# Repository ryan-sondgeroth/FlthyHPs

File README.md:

# FlthyHPs (Flthy Holoprojectors)

This repo contains the `FlthyHPs_v2.1.ino` sketch and supporting documentation for controlling 3 R2 holoprojectors (Front/Rear/Top) with:

- NeoPixel LED effects (7 LEDs per projector)
- Servo articulation through an Adafruit PCA9685 I2C board
- Auto-twitch behavior for both LEDs and servos
- Serial/I2C command control (plus optional RC input)

This README is based on the manual in [`docs/Guide to Using Your FlthyHPs v1.8 .docx`](docs/Guide%20to%20Using%20Your%20FlthyHPs%20v1.8%20.docx), with updates aligned to the current `v2.1` sketch.

## At a Glance

- **Sketch:** `FlthyHPs_v2.1.ino`
- **Arduino I2C address:** `0x19` (decimal 25)
- **PCA9685 I2C address:** `0x40` (default)
- **Serial baud:** `9600`
- **HP count:** 3 (Front, Rear, Top)

## Hardware

## PCB Renders

| Top | Isometric Front |
|-----|----------------|
|  |  |

| Isometric Back | Side |
|---------------|------|
|  |  |

---

### FlthyHPs Maestro v3 PCB (current)

The v3 system replaces the separate breakout board + PCA9685 combo with a single custom PCB: **FilthyHPs_Maestro**.

- **Arduino Pro Mini** (5V, 16MHz) — plugs into U1 headers
- **Pololu Micro Maestro 6-Channel** servo controller — plugs into U2 headers (replaces PCA9685)
- **Pololu D24V50F5** 5V 5A regulator — plugs into U3 headers
- 6 servos (2 per HP) via Maestro channels 0–5
- 3 HP NeoPixel assemblies (7 LED Jewel each) via Arduino D2/D3/D4
- I2C headers (J6, J7) for external peripherals and accepting commands from I2C controllers
- Serial header (J2) for sending commands to the Arduino sketch

**Power input:**
- 7–36V unregulated via J1 screw terminal (regulated on-board by D24V50F5)
- Or regulated 5V direct via J8 screw terminal (bypasses regulator)

**Improved circuit protection over previous versions:**
- P-ch MOSFET (Q1) ideal diode gates VIN_RAW to the servo rail, preventing backfeed
- 5.1V Zener clamps (D1, D2) protect Maestro and Arduino signal lines from overvoltage
- 500mA PTC resettable fuse (F1) on the 5V logic rail — self-resetting, no fuse to replace

**Improved power stability over previous versions:**
- Bulk capacitance across the input, servo, and logic rails absorbs current spikes and smooths supply transients
- Decoupling capacitors at key IC supply pins suppress high-frequency noise

**Simplified servo setup over previous versions:**
- Moving to the Pololu Micro Maestro eliminates the tedious per-servo position configuration previously done in the sketch
- Servo travel limits, speeds, and positions are configured visually using the Maestro Control Center application, with no sketch changes required

Servo control and calibration: [`Maestro/Maestro_Setup_Guide.md`](Maestro/Maestro_Setup_Guide.md)

### Legacy hardware (v1/v2/v2.1)

Earlier versions used a Flthy breakout board + Adafruit PCA9685 servo driver. The v2.1 sketch still supports this hardware. See [`docs/README.md`](docs/README.md) for the full legacy wiring guide.

## Wiring (Default)

### Arduino pins (v3 Maestro PCB)

- `D2` Front HP LED data
- `D3` Rear HP LED data
- `D4` Top HP LED data
- `D9` RC input (optional, if enabled)
- `D10` Maestro `RST` (servo output enable control)
- `D13` status LED
- `A4/A5` I2C SDA/SCL (to J6/J7 I2C headers)
- `TX/RX` Serial to Maestro (via J2 Serial header)

### Maestro channels (v3)

- `0/1` Front HP servos
- `2/3` Rear HP servos
- `4/5` Top HP servos

### Legacy PCA9685 channels (v1/v2/v2.1)

- `0/1` Front HP servos
- `2/3` Rear HP servos
- `4/5` Top HP servos

## Required Libraries

- `Wire` (built-in)
- [Adafruit NeoPixel](https://github.com/adafruit/Adafruit_NeoPixel)
- [Adafruit PWM Servo Driver Library](https://github.com/adafruit/Adafruit-PWM-Servo-Driver-Library)
- Big Happy Dude Slow Servo library (`Servos.h`) vendored in this repo at `libraries/SlowServoPCA9685`

Note: the standard Arduino Servo library is not used due to NeoPixel timing conflicts.

### Vendored slow-servo library

This repo includes `libraries/SlowServoPCA9685` so the required `Servos.h` dependency is versioned with the sketch.

- Source in this repo: `libraries/SlowServoPCA9685`
- License in upstream headers: GNU GPL v3 or later
- Original copyright: Graham Short (2013)

## Setup and Flashing

1. Install Arduino IDE.
2. Install required libraries.
3. Install Adafruit libraries directly from upstream repos:

```bash
./scripts/install-adafruit-libs.sh
```

4. Install vendored slow-servo library from this repo:

```bash
./scripts/install-libs.sh
```

Optional: set `ARDUINO_LIB_DIR` if your Arduino libraries path is not `~/Documents/Arduino/libraries`.

5. Open `FlthyHPs_v2.1.ino`.
6. Set board to **Arduino Pro or Pro Mini** and select your FTDI serial port.
7. Adjust configuration values (if needed).
8. Upload and verify boot behavior.

## Key Sketch Settings

Common settings called out in the manual and present in the current sketch:

- `Config::I2C_ADDRESS` (`0x19`)
- `Config::SERVO_I2C_ADDRESS` (`0x40`)
- `OUTPUT_ENABLED_PIN` (`10`)
- `BRIGHTNESS` (`150`)
- `ENABLEBASICHP` (basic vs 9-point preset coordinate mode)
- `enableTwitchLED[]` and `enableTwitchHP[]`
- `LEDTwitchInterval[][]` and `HPTwitchInterval[][]`
- `SERVO_SPEED[]`
- `Config::ENABLE_SERVO_EASING` and easing duration/update interval (v2.1)

For RC control, enable the RC option in the sketch and confirm RC pulse range values match your radio.

## Command Model

Command format:

- `DT##`
- `DT##C`
- `DT##CS`
- `DT##P`
- Optional runtime suffix: `|seconds`

Where:

- `D` = device designator: `F`, `R`, `T`, `A`, `X`, `Y`, `Z`, or `S` (special sequence set)
- `T` = type: `0` LED, `1` servo
- `##` = 2-digit sequence ID
- `C` = color (0-9)
- `S` = speed (dim pulse speed 0-9)
- `P` = position (0-8 preset)

### Color values

- `0` random
- `1` red
- `2` yellow
- `3` green
- `4` cyan
- `5` blue
- `6` magenta
- `7` orange
- `8` purple
- `9` white

### LED sequences (Type `0`)

- `D001` Leia
- `D002C` Color projector
- `D003CS` Dim pulse
- `D004C` Cycle
- `D005C` Solid color
- `D006` Rainbow
- `D007C` Short circuit
- `D096` Clear LEDs, disable auto LED, disable off-color
- `D0971` Clear LEDs, auto LED default, disable off-color
- `D0972` Clear LEDs, auto LED random, disable off-color
- `D098` Clear LEDs, disable auto LED, enable off-color
- `D0991` Clear LEDs, auto LED default, enable off-color
- `D0992` Clear LEDs, auto LED random, enable off-color

### Servo sequences (Type `1`)

- `D101P` Go to preset position (`0..8`)
- `D102` RC control left/right
- `D103` RC control up/down
- `D104` Random position
- `D105` Wag left/right
- `D106` Wag up/down
- `D198` Disable auto servo twitch
- `D199` Enable auto servo twitch

### Special `S` sequences

- `S1` Leia mode (front down + Leia LEDs, others disabled)
- `S4` Clear + disable auto, off-color disabled
- `S5` Clear + enable auto (default LED twitch), off-color disabled
- `S6` Clear + enable auto (random LED twitch), off-color disabled
- `S7` Clear + disable auto, off-color enabled
- `S8` Clear + enable auto (default LED twitch), off-color enabled
- `S9` Clear + enable auto (random LED twitch), off-color enabled

### Timed command examples

```text
A006|25     # Rainbow on all HPs for 25s
F001|60     # Leia on Front HP for 60s
T1012|10    # Move Top HP to preset 2 for 10s
```

## MarcDuino Integration (from manual)

The manual includes MarcDuino `v1.5/v2` usage over I2C. Core idea:

- Connect SDA/SCL/GND between MarcDuino and FlthyHPs controller.
- Send a string command to FlthyHPs address (`25` decimal by default).
- Example:

```text
&25,"A006|10\r
```

If another device already uses address `25`, change `Config::I2C_ADDRESS` in the sketch and update MarcDuino command address accordingly.

## Notes

- The manual in `docs/` is `v1.8`; this repo sketch is `v2.1`.
- If details conflict, treat `FlthyHPs_v2.1.ino` as source of truth.

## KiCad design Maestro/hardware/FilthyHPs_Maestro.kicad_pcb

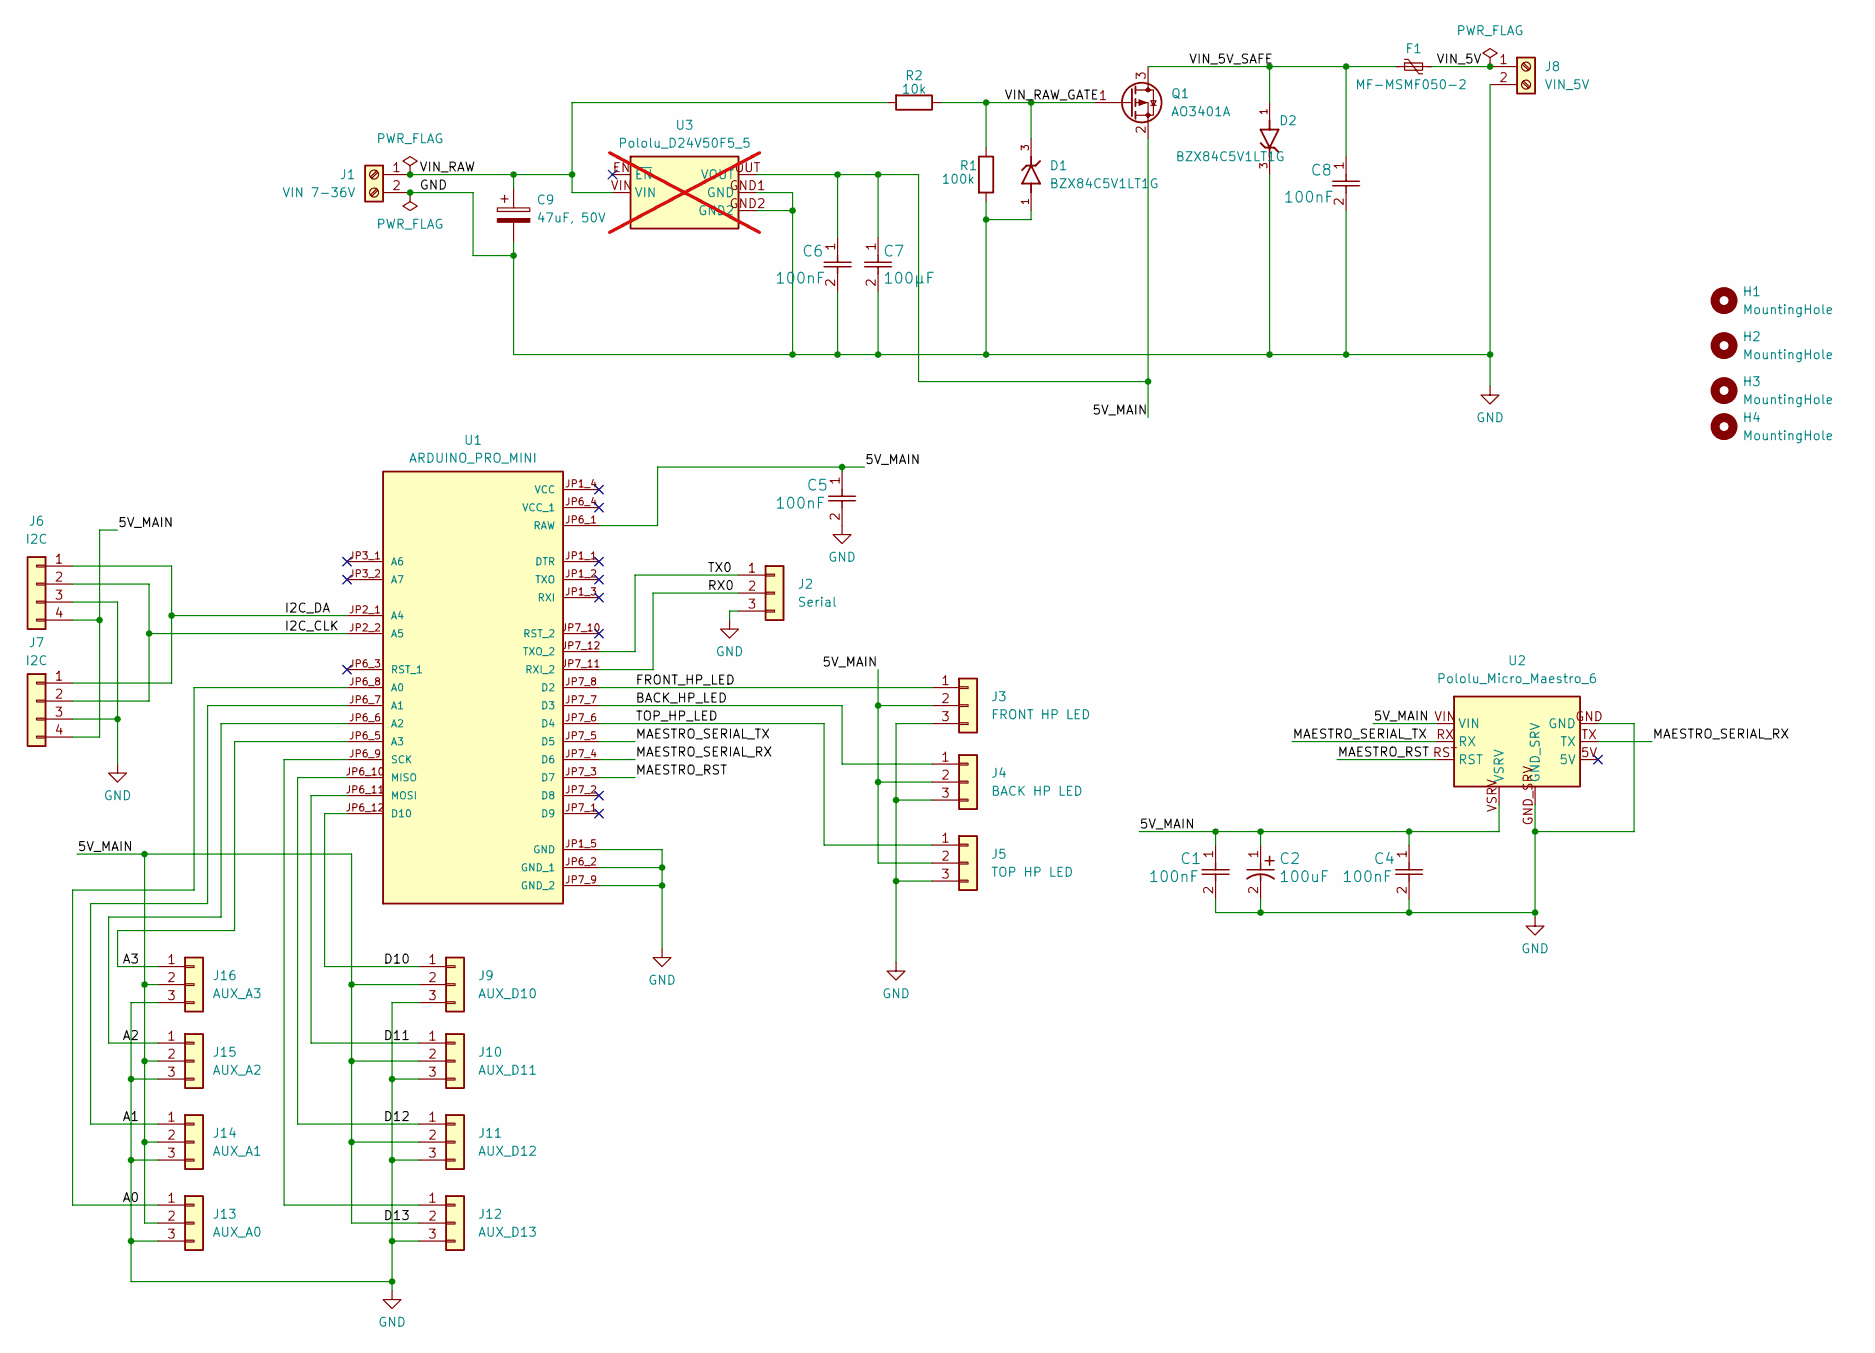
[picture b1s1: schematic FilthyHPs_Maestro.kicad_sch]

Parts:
C1, C4, C5, C6, C8: 100nF; G-188_MUR
C2: 100uF; CP_Elec_6.3x5.4; Part# DMBJ RVT1C101M0605; JLCPCB# C970684
C7: 100µF; C_0805_2012Metric_Pad1.18x1.45mm_HandSolder; Part# Samsung CL21A107MQYNNWE
C9: 47uF, 50V; CP_Elec_8x10; Part# Kemet A767KN476M1HLAE029
D1, D2: BZX84C5V1LT1G; SOT95P240X111-3N; PARTREV 23
F1: MF-MSMF050-2; Fuse_1812_4532Metric_Pad1.30x3.40mm_HandSolder
H1, H2, H3, H4: MountingHole; MountingHole_2.2mm_M2_DIN965_Pad_TopBottom
J1: VIN 7-36V; TerminalBlock_MaiXu_MX126-5.0-02P_1x02_P5.00mm
J2: Serial; PinHeader_1x03_P2.54mm_Vertical
J3: FRONT HP LED; PinHeader_1x03_P2.54mm_Vertical
J4: BACK HP LED; PinHeader_1x03_P2.54mm_Vertical
J5: TOP HP LED; PinHeader_1x03_P2.54mm_Vertical
J6, J7: I2C; PinHeader_1x04_P2.54mm_Vertical
J8: VIN_5V; TerminalBlock_MaiXu_MX126-5.0-02P_1x02_P5.00mm
J9: AUX_D10; PinHeader_1x03_P2.54mm_Vertical
J10: AUX_D11; PinHeader_1x03_P2.54mm_Vertical
J11: AUX_D12; PinHeader_1x03_P2.54mm_Vertical
J12: AUX_D13; PinHeader_1x03_P2.54mm_Vertical
J13: AUX_A0; PinHeader_1x03_P2.54mm_Vertical
J14: AUX_A1; PinHeader_1x03_P2.54mm_Vertical
J15: AUX_A2; PinHeader_1x03_P2.54mm_Vertical
J16: AUX_A3; PinHeader_1x03_P2.54mm_Vertical
Q1: AO3401A; SOT-23
R1: 100k; R_0805_2012Metric_Pad1.20x1.40mm_HandSolder
R2: 10k; R_0805_2012Metric_Pad1.20x1.40mm_HandSolder
U1: ARDUINO_PRO_MINI; MODULE_ARDUINO_PRO_MINI; PARTREV N/A
U2: Pololu_Micro_Maestro_6; Module_Pololu_Micro_Maestro_6_Mechanical
U3: Pololu_D24V50F5_5; Converter_DCDC_Pololu_D24V50F5; not fitted

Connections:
/5V_MAIN: C1.1, C2.1, C4.1, C5.1, C6.1, C7.1, J3.2, J4.2, J5.2, J6.4, J7.4, J9.2, J10.2, J11.2, J12.2, J13.2, J14.2, J15.2, J16.2, Q1.2 (S), U1.JP6_1 (RAW), U2.VIN, U2.VSRV, U3.OUT (VOUT)
/A0: J13.1, U1.JP6_8 (A0)
/A1: J14.1, U1.JP6_7 (A1)
/A2: J15.1, U1.JP6_6 (A2)
/A3: J16.1, U1.JP6_5 (A3)
/BACK_HP_LED: J4.1, U1.JP7_7 (D3)
/D10: J9.1, U1.JP6_12 (D10)
/D11: J10.1, U1.JP6_11 (MOSI)
/D12: J11.1, U1.JP6_10 (MISO)
/FRONT_HP_LED: J3.1, U1.JP7_8 (D2)
/I2C_CLK: J6.2, J7.2, U1.JP2_2 (A5)
/I2C_DA: J6.1, J7.1, U1.JP2_1 (A4)
/MAESTRO_RST: U1.JP7_3 (D7), U2.RST
/MAESTRO_SERIAL_RX: U1.JP7_4 (D6), U2.TX
/MAESTRO_SERIAL_TX: U1.JP7_5 (D5), U2.RX
/RX0: J2.2, U1.JP7_11 (RXI_2)
/TOP_HP_LED: J5.1, U1.JP7_6 (D4)
/TX0: J2.1, U1.JP7_12 (TXO_2)
/VIN_5V: F1.2, J8.1
/VIN_5V_SAFE: C8.1, D2.1, F1.1, Q1.3 (D)
/VIN_RAW: C9.1, J1.1, R2.2, U3.VIN
/VIN_RAW_GATE: D1.3, Q1.1 (G), R1.1, R2.1
GND: C1.2, C2.2, C4.2, C5.2, C6.2, C7.2, C8.2, C9.2, D1.1, D2.3, J1.2, J2.3, J3.3, J4.3, J5.3, J6.3, J7.3, J8.2, J9.3, J10.3, J11.3, J12.3, J13.3, J14.3, J15.3, J16.3, R1.2, U1.JP1_5 (GND), U1.JP1_6 (GND), U1.JP6_2 (GND_1), U1.JP7_9 (GND_2), U2.GND, U2.GND_SRV, U3.GND1 (GND), U3.GND2
unnamed: J12.1, U1.JP6_9 (SCK)

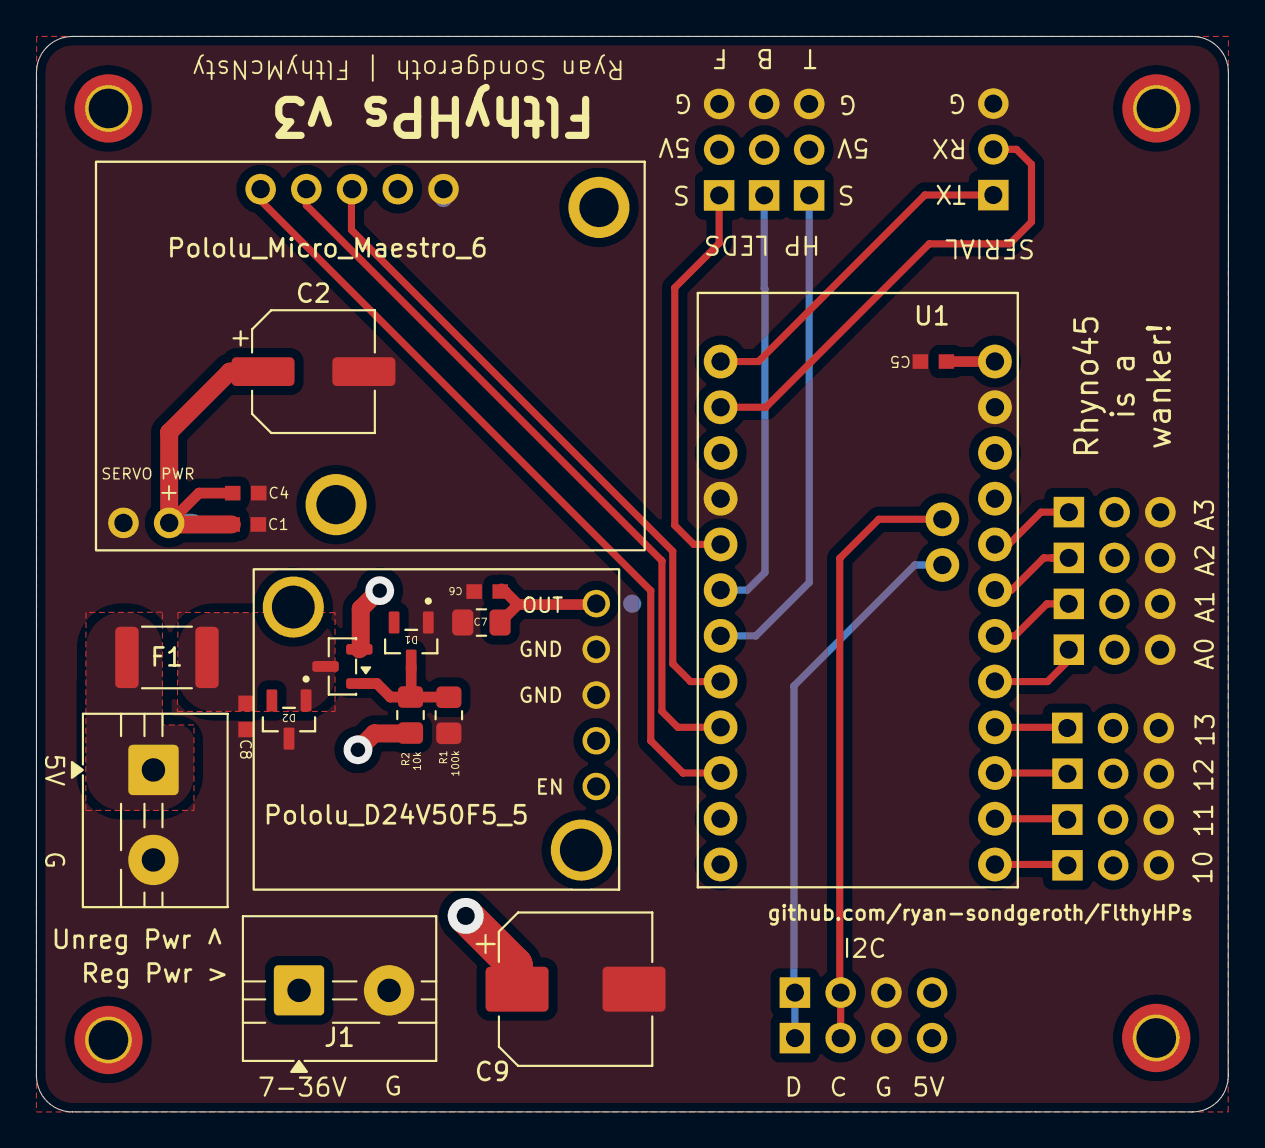
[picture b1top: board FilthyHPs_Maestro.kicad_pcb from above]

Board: 2 copper layers, 66.2 x 59.8 mm, 37 parts (0 on the bottom side), 24 nets.

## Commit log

2026-03-03 File Seed
2026-03-03 Add README.md for FlthyHPs project detailing features, hardware requirements, wiring, installation, configuration, and command reference
2026-03-03 Added additional docs
2026-03-03 Remove outdated guide for FlthyHPs v1.8
2026-03-03 Removes old text extract
2026-03-03 Update README.md to indicate ongoing work in progress
2026-03-03 Add multiple new images to the manual documentation
2026-03-03 Update documentation to reflect recent changes and improvements
2026-03-03 Update README.md for clarity and organization
2026-03-03 Add installation scripts and vendored SlowServoPCA9685 library
2026-03-03 Refactor Serial initialization comment and disable IntelliSense linter
2026-03-26 Update repo to include sketch that supports Pololu Maestro servo control.
2026-03-26 Update Maestro setup guide for improved clarity and detail in channel assignments and subroutine references
2026-03-27 Add hardware files and fabrication data for FilthyHPs Maestro project
2026-03-27 Update README.md with additional power input options and component details
2026-03-27 Update README.md to clarify the purpose of the Serial header for Arduino sketch commands
2026-03-27 Enhance README.md with detailed power input options and improved circuit protection and stability descriptions
2026-03-27 Update README.md to clarify I2C headers functionality and improve power stability descriptions
2026-03-27 Update README.md to simplify servo setup description and clarify I2C header usage
2026-03-27 Update .gitignore to include board design files and related artifacts
2026-03-27 Remove obsolete hardware files and fabrication artifacts from the repository
2026-03-27 Update .gitignore to include additional fabrication file types
2026-03-27 Remove outdated references to KiCad project and fabrication files in README.md
2026-04-07 Enhance setup guide and settings script with clearer instructions and additional grep commands for file management
2026-04-07 Fix formatting in maestro_settings.txt by adding missing script tags
2026-04-07 Clarify instructions for updating the script section in the setup guide and modify the script tag in maestro_settings.txt to include attributes
2026-04-07 Update subroutine termination in scripts and enhance setup guide instructions
2026-04-07 Refactor FlthyHPs Maestro Script to use named pose subroutines and add custom routine for clockwise tour
2026-04-07 Update comments in Maestro script and setup guide for clarity on subroutine usage and custom routines
